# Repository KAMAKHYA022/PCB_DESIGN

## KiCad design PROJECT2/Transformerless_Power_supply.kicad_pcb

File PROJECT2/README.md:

# Transformerless AC to DC 5V Converter

This project demonstrates how to convert **220V AC to 5V DC** without using a transformer. Instead, it relies on a **capacitive dropper circuit** to reduce voltage before rectification and regulation.

---

## 📌 Table of Contents
- [Introduction](#introduction)
- [Why Transformerless Power Supply?](#why-transformerless-power-supply)
- [Circuit Diagram](#circuit-diagram)
- [Working Principle](#working-principle)
- [Components Required](#components-required)
- [PCB Design](#pcb-design)
- [Simulation](#simulation)
- [Precautions](#precautions)
- [References](#references)

---

## 🔹 Introduction
Traditional AC to DC converters use transformers to step down voltage. However, in **low-power applications**, a transformerless power supply is a cost-effective alternative. This circuit converts **220V AC** to **5V DC** safely using a capacitor, rectifier, and voltage regulator.

---

## 🔹 Why Transformerless Power Supply?
✔ **Compact Design** – No bulky transformer, making it ideal for space-limited applications.  
✔ **Cost-Effective** – Eliminates the need for expensive transformers.  
✔ **Efficient for Low Current Applications** – Suitable for circuits requiring small current (e.g., microcontrollers, small sensors).  

---

## 🔹 Circuit Diagram
📌 **[Click here to view the schematic](schematic.JPG)**  

---

## 🔹 Working Principle
1. **Voltage Dropping**  
   - **C1 (X-rated capacitor)** drops the **220V AC** voltage while limiting current.  
   - **R1 (Bleeder resistor)** discharges C1 when unplugged, preventing shock hazards.  

2. **Rectification**  
   - **Bridge Rectifier (D1 - D4)** converts AC to pulsating DC.  

3. **Smoothing**  
   - **C2 (Electrolytic capacitor)** filters the pulsating DC.  

4. **Voltage Regulation**  
   - **7805 voltage regulator** ensures a stable **5V output**.  

---

## 🔹 Components Required
| Component | Specification | Quantity |
|-----------|--------------|----------|
| X-rated Capacitor | 0.47µF, 400V | 1 |
| Resistor | 470KΩ | 1 |
| Resistor | 1KΩ | 1 |
| Diode | 1N4007 | 4 |
| Electrolytic Capacitor | 1000µF, 25V | 1 |
| Ceramic Capacitor | 0.1µF | 1 |
| Voltage Regulator | 7805 | 1 |
| LED | Indicator | 1 |

---

## 🔹 PCB Design
📌 **[Click here to view the PCB layout](pcb_layout.JPG)**  

---

## 🔹 Simulation
- The circuit is tested in **Proteus** and verified for stable **5V DC output**.  
- 📌 **[Click here to view simulation results](simulation.JPG)**  

---

## ⚠️ Precautions
❗ **High Voltage Warning:** This circuit operates at **220V AC**, which can be lethal. Always follow safety precautions:  
✔ **Do not touch the circuit when powered.**  
✔ **Use insulated gloves when testing.**  
✔ **Always discharge capacitors before handling.**  

---

## 📚 References
- Transformerless power supply design articles.  
- Datasheets for **7805, 1N4007 diodes, and X-rated capacitors**.  

---

### 📌 **Note**  
This project is suitable for **low-power applications** like microcontroller circuits, sensor modules, and LED indicators. Do **not** use it for high-current devices.  

---

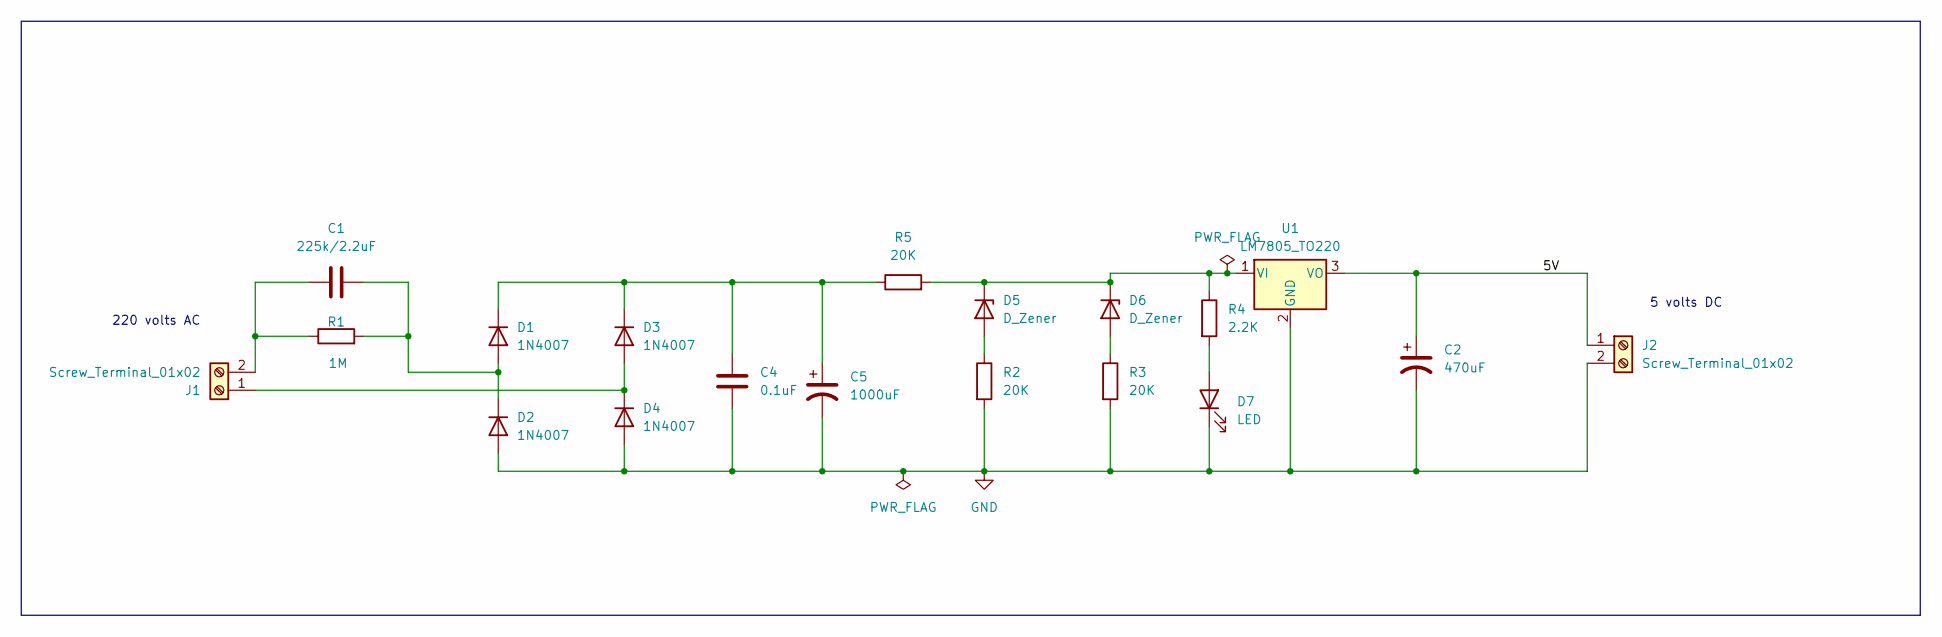
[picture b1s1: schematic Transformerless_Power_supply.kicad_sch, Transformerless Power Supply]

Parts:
C1: 225k/2.2uF; C_Rect_L18.0mm_W6.0mm_P15.00mm_FKS3_FKP3
C2: 470uF; CP_Radial_D10.0mm_P3.80mm
C4: 0.1uF; C_Disc_D4.7mm_W2.5mm_P5.00mm
C5: 1000uF; CP_Radial_D10.0mm_P5.00mm
D1, D2, D3, D4: 1N4007; D_DO-41_SOD81_P10.16mm_Horizontal
D5, D6: D_Zener; D_A-405_P7.62mm_Horizontal
D7: LED; LED_D5.0mm
J1, J2: Screw_Terminal_01x02; TerminalBlock_bornier-2_P5.08mm
R1: 1M; R_Axial_DIN0207_L6.3mm_D2.5mm_P7.62mm_Horizontal
R2, R3, R5: 20K; R_Axial_DIN0207_L6.3mm_D2.5mm_P7.62mm_Horizontal
R4: 2.2K; R_Axial_DIN0207_L6.3mm_D2.5mm_P7.62mm_Horizontal
U1: LM7805_TO220; TO-220-3_Vertical

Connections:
/5V: C2.1, J2.1, U1.3 (VO)
GND: C2.2, C4.2, C5.2, D2.2 (A), D4.2 (A), D7.1 (K), J2.2, R2.2, R3.2, U1.2 (GND)
unnamed: C1.2, D1.2 (A), D2.1 (K), R1.2
unnamed: C4.1, C5.1, D1.1 (K), D3.1 (K), R5.1
unnamed: D3.2 (A), D4.1 (K), J1.1
unnamed: D5.2 (A), R2.1
unnamed: D5.1 (K), D6.1 (K), R4.1, R5.2, U1.1 (VI)
unnamed: D6.2 (A), R3.1
unnamed: D7.2 (A), R4.2
unnamed: C1.1, J1.2, R1.1

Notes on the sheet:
220 volts AC
5 volts DC

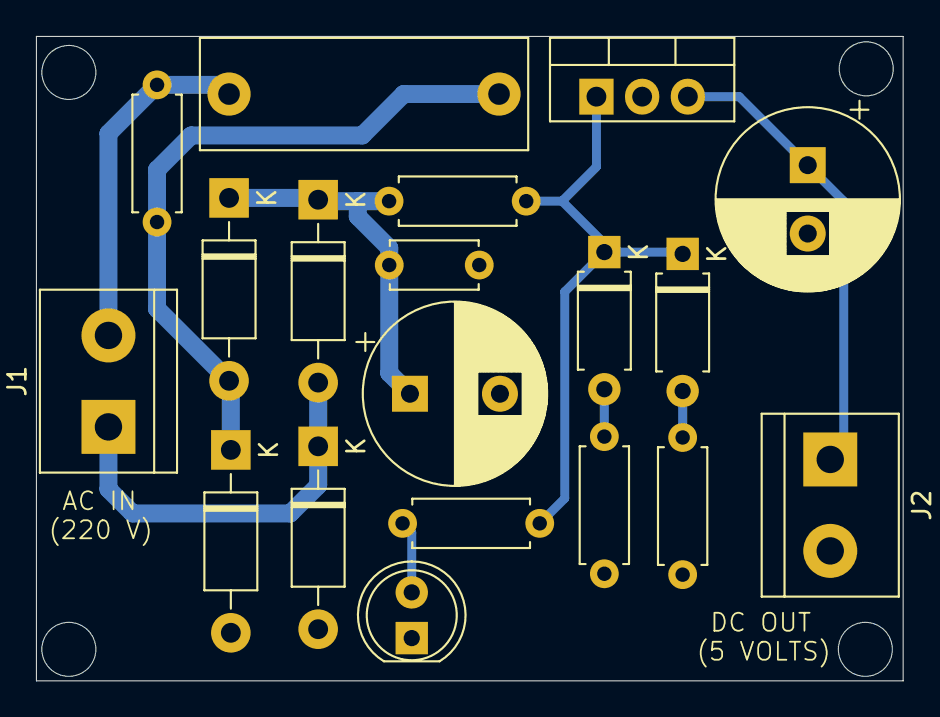
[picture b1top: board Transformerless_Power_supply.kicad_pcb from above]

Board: 2 copper layers, 48.2 x 35.8 mm, 19 parts (0 on the bottom side), 10 nets.

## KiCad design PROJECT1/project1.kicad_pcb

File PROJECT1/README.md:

##  Designing a 12V AC to DC Converter

  For this project, we design a 12V AC to DC Converter using KiCad for schematic and PCB design. The circuit includes a transformer, full-wave rectifier, smoothing capacitor, voltage regulator, and LED 
  indicator.

  Components Used:

  Transformer (X1) – Steps down 220V AC to 12V AC.

  Bridge Rectifier (D1-D4, 1N4007 diodes) – Converts AC to pulsating DC.

  Capacitor (C1, 1000µF) – Smooths the pulsating DC.

  Voltage Regulator (U1, 7812 IC) – Provides a steady 12V DC output.

  Resistors (R1, R2) – Current limiting resistors for circuit protection.

  LED Indicator (D5) – Shows power status.

## 5. PCB Design in KiCad

  The schematic is designed in KiCad, ensuring correct component placement and PCB layout. The PCB layout is optimized to minimize noise and improve efficiency.
## Designing a 12V AC to DC Converter

### Schematic Design in KiCad

### PCB Layout

### PCB 3D View

### Simulation in Proteus

## 6. Simulation in Proteus

To verify circuit functionality before manufacturing, the schematic is simulated in Proteus:

Transformer steps down 220V AC to 12V AC.

Bridge rectifier converts AC to DC.

Capacitor smooths the DC voltage.

IC 7812 ensures a regulated 12V DC output.

LED indicates circuit operation.

## 7. Why These Components Were Chosen?

7812 Voltage Regulator – Provides a steady 12V DC output with overvoltage protection.

1000µF Capacitor – Smooths rectified DC to reduce ripple.

10Ω Resistor (R2) – Helps with voltage stabilization.

2.2kΩ Resistor (R1) with LED – Limits current to the LED for indicating circuit operation.

## 8. Conclusion

This AC to DC converter provides a regulated 12V DC output from 220V AC input. The design ensures efficiency and reliability for powering various electronics. The project demonstrates PCB design, simulation, and implementation of a real-world power supply circuit.

Future Improvements:

Adding a heat sink to the 7812 regulator for better thermal management.

Designing a dual-output version for 5V and 12V DC supplies.

Implementing a switching regulator for better efficiency.

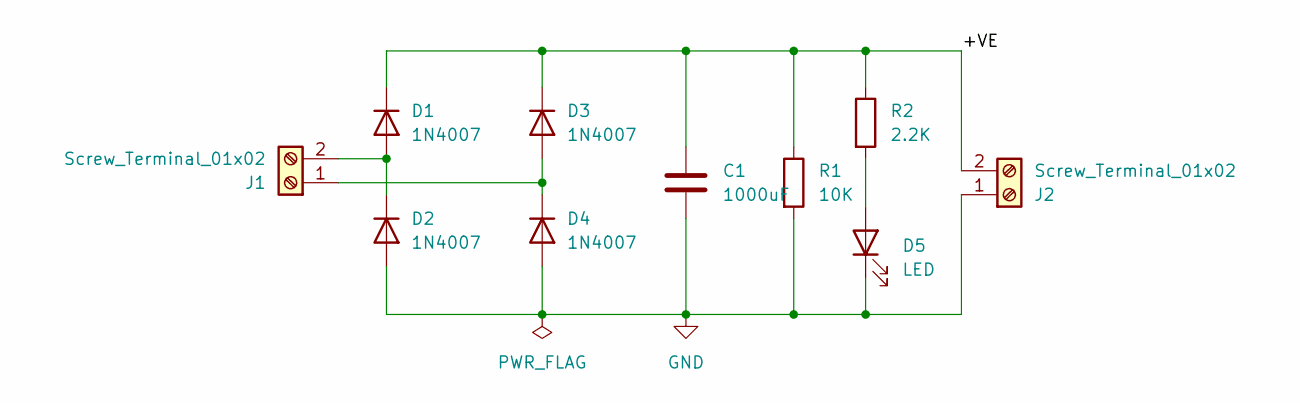
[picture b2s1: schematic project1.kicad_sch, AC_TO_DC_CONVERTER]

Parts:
C1: 1000uF; C_Radial_D8.0mm_H11.5mm_P3.50mm
D1, D2, D3, D4: 1N4007; D_DO-41_SOD81_P10.16mm_Horizontal
D5: LED; LED_D5.0mm
J1, J2: Screw_Terminal_01x02; TerminalBlock_bornier-2_P5.08mm
R1: 10K; R_Axial_DIN0204_L3.6mm_D1.6mm_P7.62mm_Horizontal
R2: 2.2K; R_Axial_DIN0204_L3.6mm_D1.6mm_P7.62mm_Horizontal

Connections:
/+VE: C1.1, D1.1 (K), D3.1 (K), J2.2, R1.1, R2.1; also elsewhere on the board
GND: C1.2, D2.2 (A), D4.2 (A), D5.1 (K), J2.1, R1.2; also elsewhere on the board
unnamed: D1.2 (A), D2.1 (K), J1.2
unnamed: D3.2 (A), D4.1 (K), J1.1
unnamed: D5.2 (A), R2.2

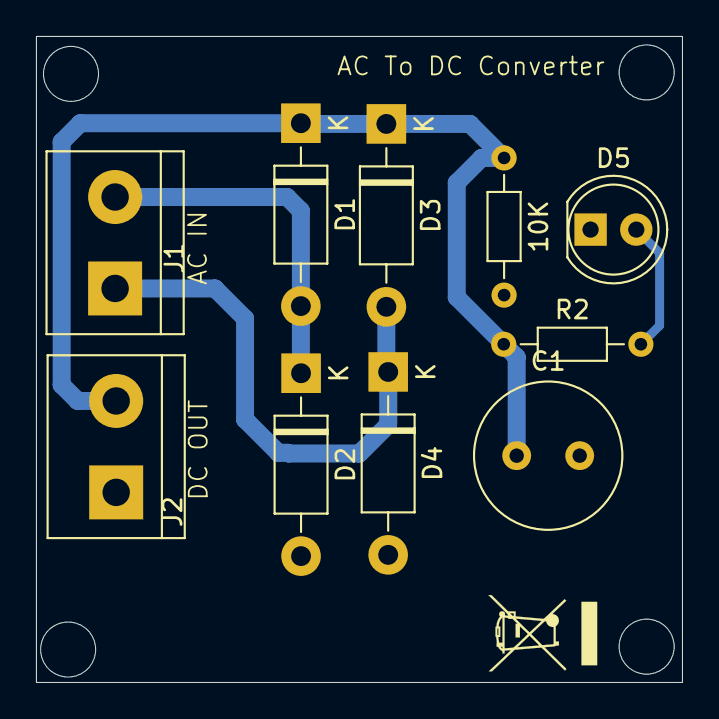
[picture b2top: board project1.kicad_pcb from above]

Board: 2 copper layers, 35.9 x 35.9 mm, 10 parts (0 on the bottom side), 5 nets.

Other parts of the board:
10K: R; R_Axial_DIN0204_L3.6mm_D1.6mm_P7.62mm_Horizontal

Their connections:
/+VE: 10K.1; also elsewhere on the board
GND: 10K.2; also elsewhere on the board

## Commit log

2025-04-01 Added projects
2025-04-01 Added projects kicad files
2025-04-01 readme file for ac to dc 12 volt added
2025-04-01 readme file for ac to dc 5 volt added
